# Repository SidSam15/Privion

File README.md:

# Privion

Data privacy is more important now than ever before. But wait- your phone is listening to you along with every other IoT device you have. We needed to design a product in order to mitigate these breaches of privacy and confidentiality. Our product, Deadzone, allows us to protect privacy by using an algorithm to construct an anti-wave to the sound wave of someone talking: this ensures that you can be safe from your own devices. 

## Inspiration

We were inspired by the lack of security in IoT systems. 

## What it does

It protects users by preventing their devices from listening to them.

## How we built it

We used raw html to create the web app and a python CV library.

## Challenges we ran into

We ran into a problem where the sound that was made was too loud when canceling out the voice so people could hear it.

## Accomplishments that we're proud of

The voice gets scrambled, and it is hard to tell what the person is saying, and the sound is quiet.

## What we learned

We learned how to use CV and integrate sensors with virtualized hardware. We also learned how canceling out sound waves work.

## What's next for Privion
   
Privion is working towards creating physical devices and making it compatible with many different devices. We also plan integrating kmk coding for full functionality.

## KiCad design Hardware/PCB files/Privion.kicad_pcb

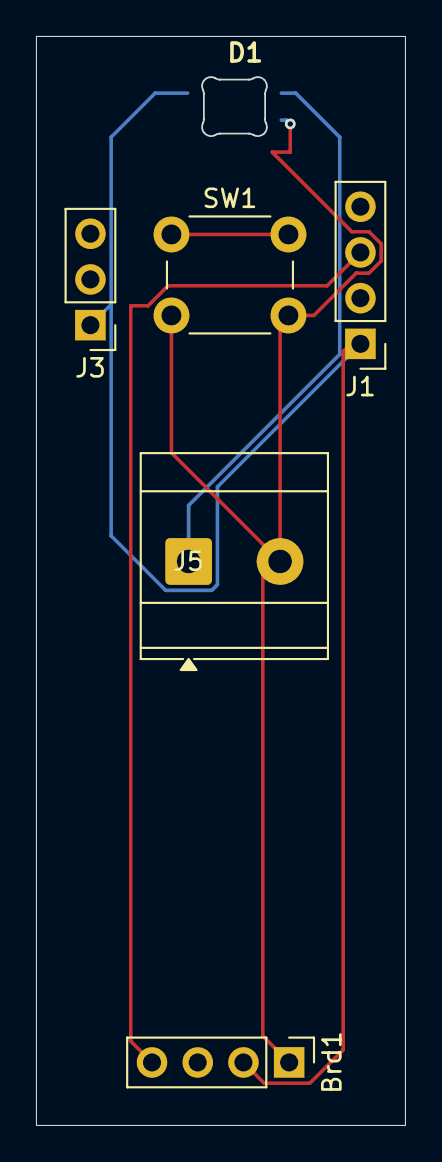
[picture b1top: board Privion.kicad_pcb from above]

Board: 2 copper layers, 20.4 x 60.5 mm, 6 parts (0 on the bottom side), 4 nets.

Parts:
Brd1: SSD1306; PinHeader_1x04_P2.54mm_Vertical
D1: SK6812MINI-E; SK6812MINI-E_fixed
J1: Conn_02x20_Odd_Even; PinHeader_1x04_P2.54mm_Vertical
J3: Conn_01x03; PinHeader_1x03_P2.54mm_Vertical
J5: Conn_01x02; TerminalBlock_Phoenix_MKDS-3-2-5.08_1x02_P5.08mm_Horizontal
SW1: SW_Push; SW_PUSH_6mm

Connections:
GND: Brd1.1 (GND), D1.3 (VSS), J5.2, SW1.2
GPIO2: Brd1.4 (SDA), J1.3
GPIO18: D1.4 (DIN), J5.1
LEDPOWER: Brd1.2 (VCC), D1.1 (VDD), J1.1, J3.1

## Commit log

2026-03-29 readme
